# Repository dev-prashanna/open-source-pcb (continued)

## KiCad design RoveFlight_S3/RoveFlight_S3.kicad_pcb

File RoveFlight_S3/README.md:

# RoveFlight S3

**RF-S3-A0 — compact ESP32-S3 flight-controller engineering prototype for a 1S brushed quadcopter.**

Hardware layout release completed 2026-11-09: **ERC 0, DRC 0, unconnected items 0, schematic/PCB parity issues 0**, with all 15 independent connectivity checks passing. [Manufacturing package](fabrication/) and [validation evidence](docs/Manufacturing_Readiness.md) are included. Via-in-pad filling/capping and fabricator DFM are required; physical qualification remains open.

A real native KiCad design with ESP32-S3-WROOM-1-N8R2, four independent brushed-motor MOSFET stages, a hardware arming latch and watchdog, BMI270 SPI IMU, BMP390 SPI barometer, battery voltage/current monitoring, downward VL53L1X, IR receiver, USB-C and receiver/optical-flow/debug expansion.

Open **RoveFlight_S3.kicad_pro** in KiCad 10. The root schematic links the functional sheets. The PCB is 45 x 45 mm, six layers, nominal 1.0-mm thickness, two-sided assembly, with 25.5-mm-square M2 mounting and an antenna overhang. The assembled antenna extends 6.75 mm beyond the forward edge. No flight-ready, fabricated-board, RF, thermal or EMC qualification is claimed.

## Electrical limits

- Protected 1S LiPo, 3.1–4.2 V. No onboard charger or cell-protection IC.
- Brushed motors only. Proposed envelope: 1 A continuous per motor, 4 A aggregate, 2 A single-channel stall for at most 100 ms, subject to actual motor/propeller and thermal qualification.
- All external signals are 3.3 V. Receiver supply/interface compatibility must be checked; no 5-V UART tolerance or SBUS inverter is provided.
- Remove JP1 to disconnect motor enable physically. USB insertion clears the arming latch. Every detected fault requires a fresh arming command; see the exact reset caveat in the safety document.
- Local attitude stabilization, failsafes, calibration, PID, mixing, telemetry, configuration, OTA and logging require firmware. The supplied bring-up skeleton only holds motors disabled and blinks the status LED.

## Engineering documentation

- [Motor numbering, calculations and interlock](docs/Motors_and_Safety.md)
- [Battery and power architecture](docs/Power_Architecture.md)
- [GPIO allocation](docs/GPIO_Allocation.md)
- [Sensor orientation and mechanics](docs/Sensors_and_Mechanics.md)
- [Recommended firmware architecture](docs/Firmware_Architecture.md)
- [Bring-up and qualification procedure](docs/Bringup_and_Validation.md)
- [Manufacturing readiness](docs/Manufacturing_Readiness.md)

BOM.csv and BOM_Grouped.csv include part numbers and footprint assignments. GPIO_Allocation.csv, Connector_Pinouts.csv and Placement.csv provide machine-readable implementation references. Manufacturer sources are recorded in datasheets/sources.json. Manufacturer catalogue listing was checked for the N8R2 variant; no distributor stock reservation or guaranteed BOM availability is claimed.

The N8R2 variant provides 8-MB Quad SPI flash and 2-MB Quad PSRAM in an 18 x 25.5 x 3.1-mm module. N8 without PSRAM was considered but leaves less buffering for logs/telemetry; N8R8 adds memory and a different memory configuration without a need in this initial design. Neither is an automatic assembly substitution. The antenna carrier-board keepout follows the official module footprint and Espressif hardware guidelines; frame, battery and wiring clearance still need RF validation.

## Construction and verification

To check and export the current design without rebuilding its placement or routing, run `python scripts/release.py` in the configured Python environment. It gates manufacturing exports on ERC, DRC, parity and connectivity checks. Verify the resulting package from this directory with `sha256sum -c fabrication/SHA256SUMS`.

Scripts require KiCad 10 system Python bindings and requirements.txt. The project was initialized and the controller instantiated through the connected KiCad MCP server; native Python construction expands the complete hierarchical schematic and board using installed KiCad libraries and an explicit pin-to-net manifest. MCP/CLI ERC and DRC provide independent validation.

The construction sequence is build_design.py -> KiCad XML netlist export -> layout.py -> prepare_routing.py -> assisted Specctra routing -> import_routing.py -> any documented repairs -> silkscreen.py -> audit_design.py and final ERC/DRC/export. **build_design.py rebuilds the schematic; layout.py clears routing. Work on a copy when experimenting.** These are engineering construction scripts, not a flight-qualified unattended release pipeline.

Original project assets are licensed under CERN-OHL-P-2.0; see LICENSE. KiCad library-derived content retains its upstream licence and exception, recorded in libraries/README.md and libraries/KiCad-LICENSE.md.

[Bottom assembly preview](previews/PCB_bottom.png). Renders show assigned library models; missing connector/sensor models are represented by their board land patterns.

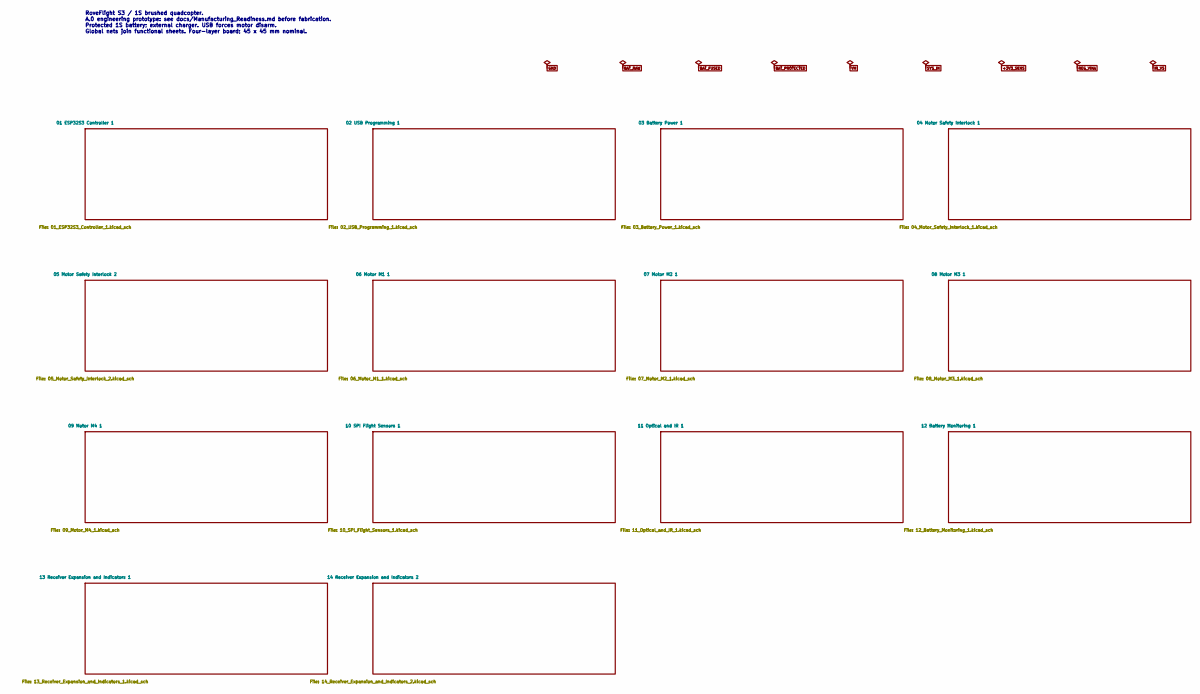
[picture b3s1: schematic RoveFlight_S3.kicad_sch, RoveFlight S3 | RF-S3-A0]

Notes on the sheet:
RoveFlight S3 / 1S brushed quadcopter. A.0 engineering prototype: see docs/Manufacturing_Readiness.md before fabrication. Protected 1S battery; external charger. USB forces motor disarm. Global nets join functional sheets. Four-layer board; 45 x 45 mm nominal.

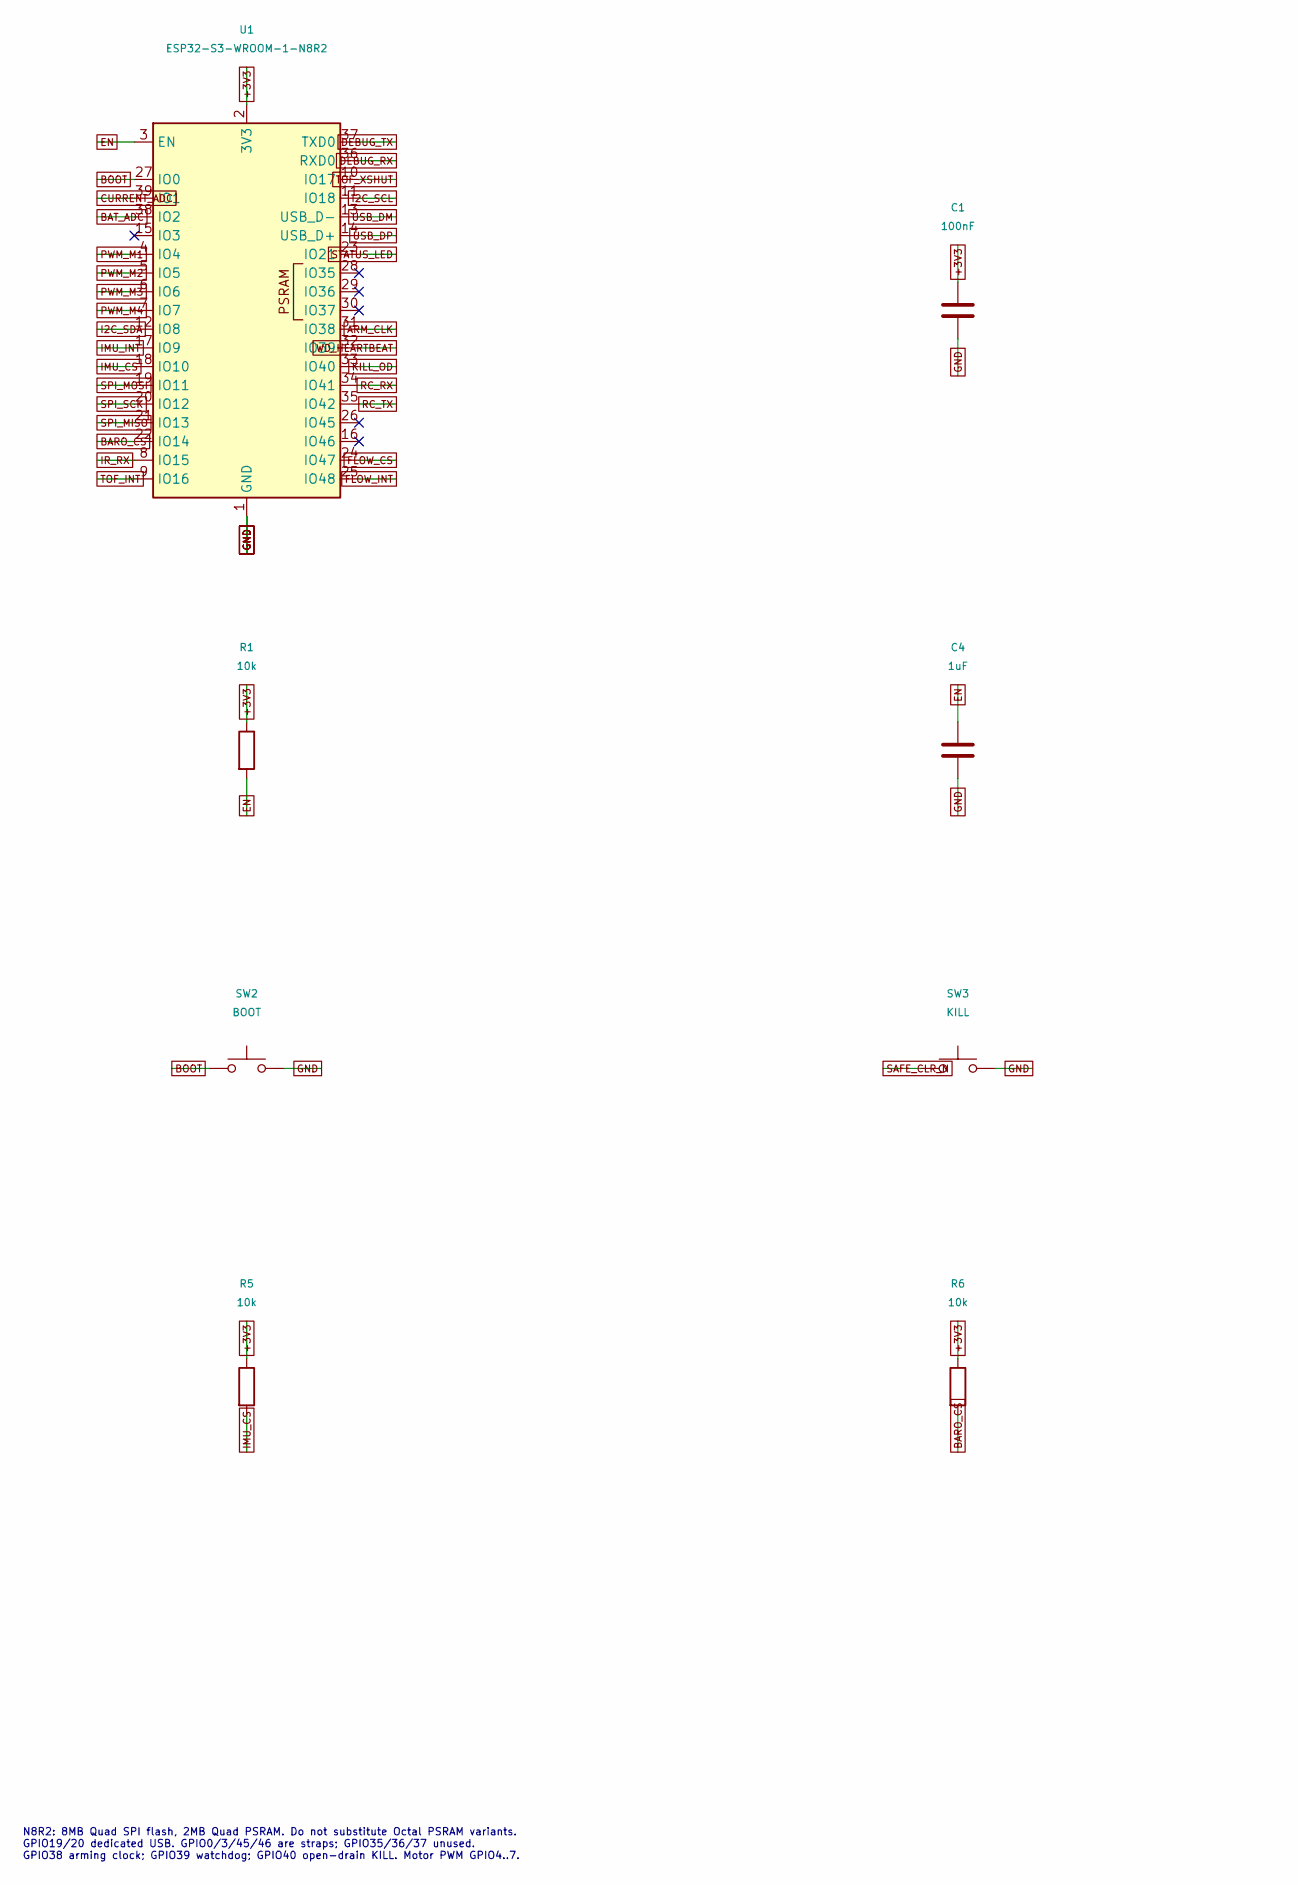
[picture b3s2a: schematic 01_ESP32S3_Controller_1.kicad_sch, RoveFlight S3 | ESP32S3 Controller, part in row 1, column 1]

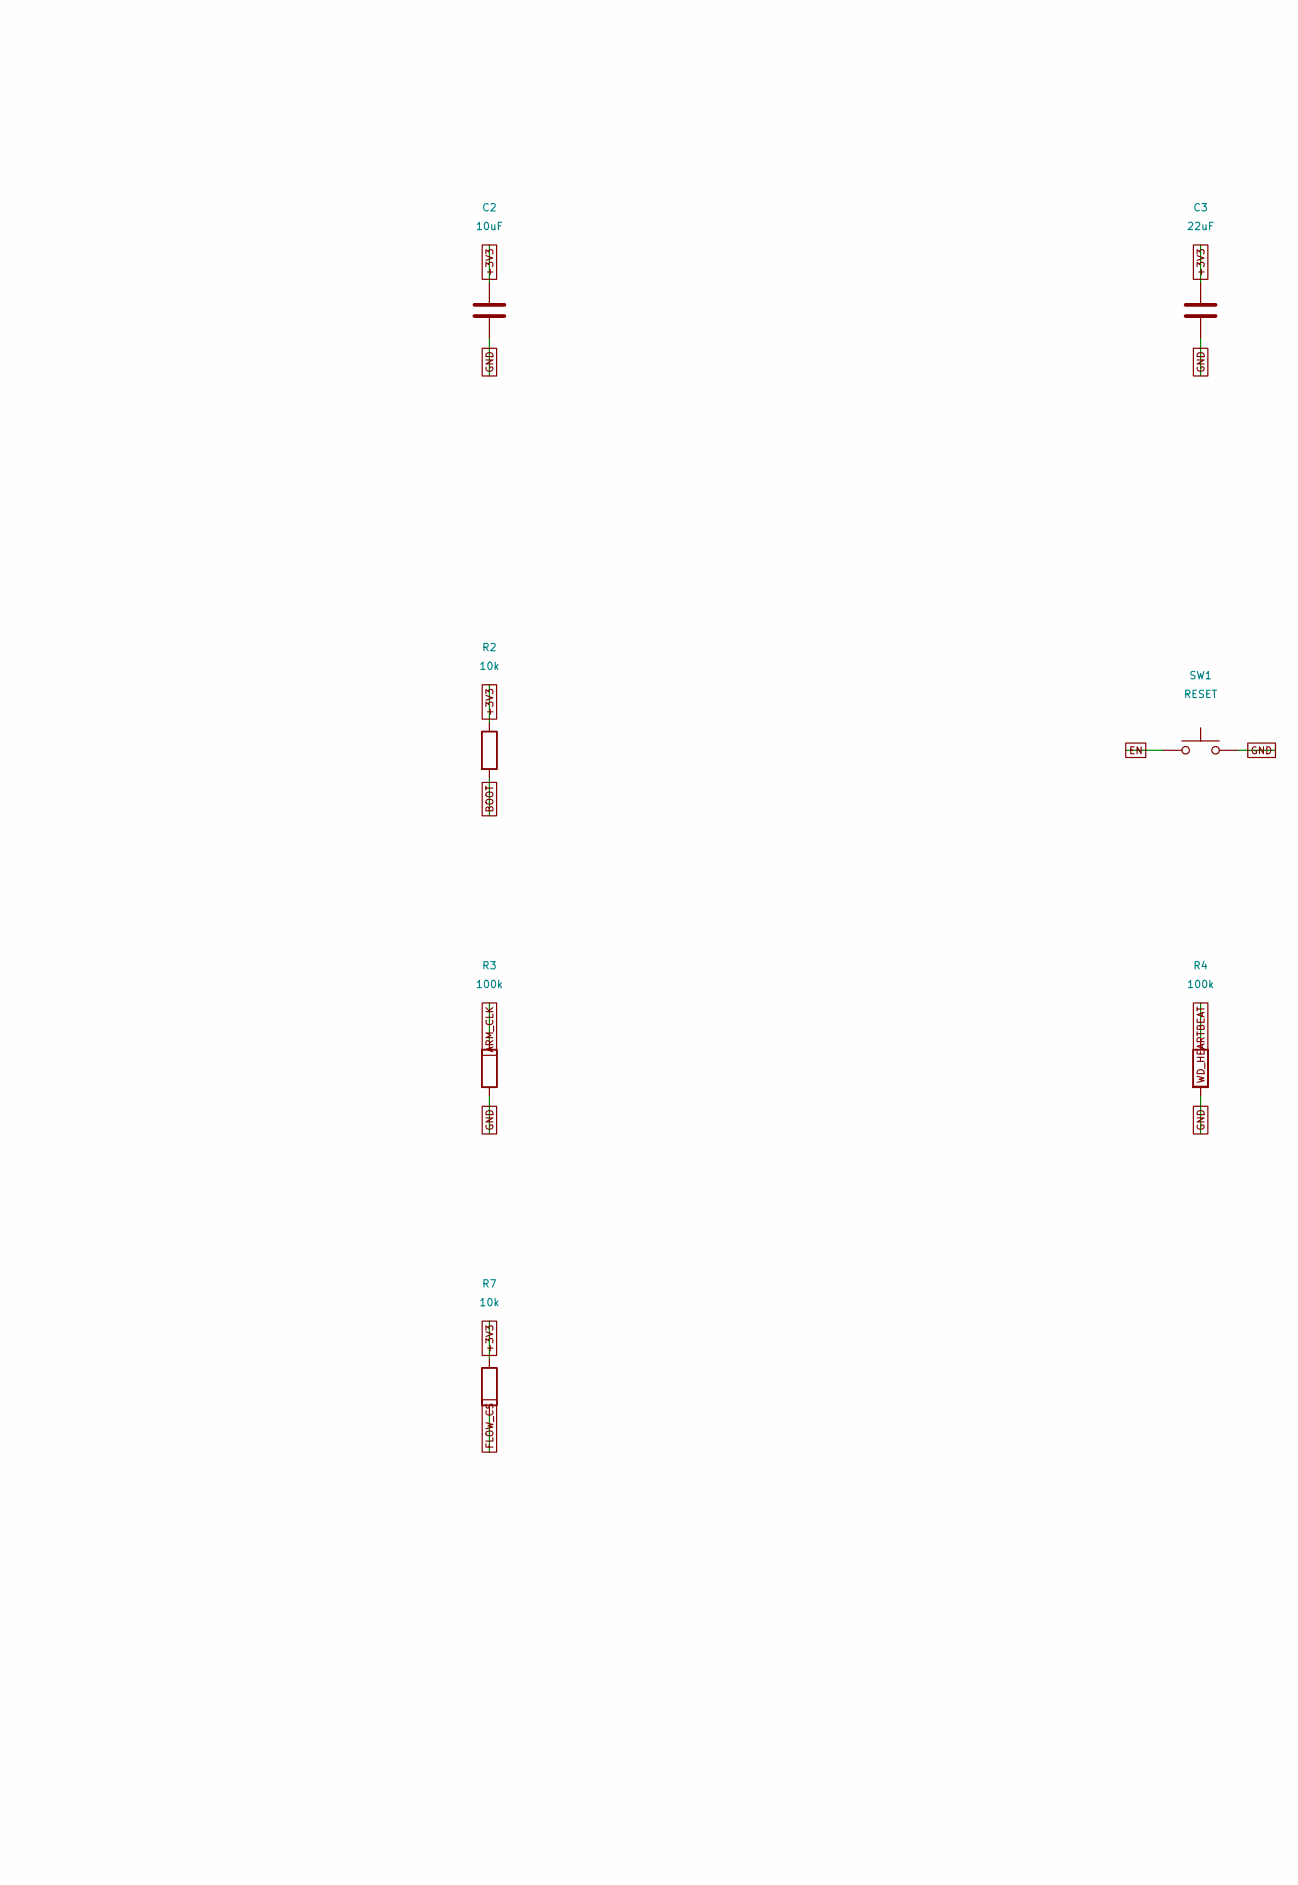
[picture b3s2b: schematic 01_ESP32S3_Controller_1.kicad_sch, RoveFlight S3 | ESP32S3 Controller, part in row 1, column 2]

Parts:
C1: 100nF; C_0402_1005Metric_RF_C1; MPN GRM155R71C104KA88D
C2: 10uF; C_0603_1608Metric; MPN GRM188R60J106ME47D
C3: 22uF; C_0805_2012Metric; MPN GRM21BR60J226ME39L
C4: 1uF; C_0402_1005Metric_RF_C4; MPN GRM155R61A105KE15D
R1: 10k; R_0402_1005Metric_RF_R1; MPN RC0402FR-071002L
R2: 10k; R_0402_1005Metric_RF_R2; MPN RC0402FR-071002L
R3: 100k; R_0402_1005Metric_RF_R3; MPN RC0402FR-071003L
R4: 100k; R_0402_1005Metric_RF_R4; MPN RC0402FR-071003L
R5: 10k; R_0402_1005Metric_RF_R5; MPN RC0402FR-071002L
R6: 10k; R_0402_1005Metric_RF_R6; MPN RC0402FR-071002L
R7: 10k; R_0402_1005Metric_RF_R7; MPN RC0402FR-071002L
SW1: RESET; SW_Push_1P1T-SH_NO_CK_KMR2xxG; MPN KMR221GLFS
SW2: BOOT; SW_Push_1P1T-SH_NO_CK_KMR2xxG; MPN KMR221GLFS
SW3: KILL; SW_Push_1P1T-SH_NO_CK_KMR2xxG; MPN KMR221GLFS
U1: ESP32-S3-WROOM-1-N8R2; ESP32-S3-WROOM-1_Overhang; MPN ESP32-S3-WROOM-1-N8R2

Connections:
+3V3: C1.1, C2.1, C3.1, R1.1, R2.1, R5.1, R6.1, R7.1, U1.2 (3V3); also elsewhere on the board
ARM_CLK: R3.1, U1.31 (IO38); also elsewhere on the board
BARO_CS: R6.2, U1.22 (IO14); also elsewhere on the board
BAT_ADC: U1.38 (IO2); also elsewhere on the board
BOOT: R2.2, SW2.1, U1.27 (IO0); also elsewhere on the board
CURRENT_ADC: U1.39 (IO1); also elsewhere on the board
DEBUG_RX: U1.36 (RXD0); also elsewhere on the board
DEBUG_TX: U1.37 (TXD0); also elsewhere on the board
EN: C4.1, R1.2, SW1.1, U1.3 (EN); also elsewhere on the board
FLOW_CS: R7.2, U1.24 (IO47); also elsewhere on the board
FLOW_INT: U1.25 (IO48); also elsewhere on the board
GND: C1.2, C2.2, C3.2, C4.2, R3.2, R4.2, SW1.2, SW2.2, SW3.2, U1.1 (GND), U1.40 (GND), U1.41 (GND); also elsewhere on the board
I2C_SCL: U1.11 (IO18); also elsewhere on the board
I2C_SDA: U1.12 (IO8); also elsewhere on the board
IMU_CS: R5.2, U1.18 (IO10); also elsewhere on the board
IMU_INT: U1.17 (IO9); also elsewhere on the board
IR_RX: U1.8 (IO15); also elsewhere on the board
KILL_OD: U1.33 (IO40); also elsewhere on the board
PWM_M1: U1.4 (IO4); also elsewhere on the board
PWM_M2: U1.5 (IO5); also elsewhere on the board
PWM_M3: U1.6 (IO6); also elsewhere on the board
PWM_M4: U1.7 (IO7); also elsewhere on the board
RC_RX: U1.34 (IO41); also elsewhere on the board
RC_TX: U1.35 (IO42); also elsewhere on the board
SAFE_CLR_N: SW3.1; also elsewhere on the board
SPI_MISO: U1.21 (IO13); also elsewhere on the board
SPI_MOSI: U1.19 (IO11); also elsewhere on the board
SPI_SCK: U1.20 (IO12); also elsewhere on the board
STATUS_LED: U1.23 (IO21); also elsewhere on the board
TOF_INT: U1.9 (IO16); also elsewhere on the board
TOF_XSHUT: U1.10 (IO17); also elsewhere on the board
USB_DM: U1.13 (USB_D-); also elsewhere on the board
USB_DP: U1.14 (USB_D+); also elsewhere on the board
WD_HEARTBEAT: R4.1, U1.32 (IO39); also elsewhere on the board

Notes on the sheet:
N8R2: 8MB Quad SPI flash, 2MB Quad PSRAM. Do not substitute Octal PSRAM variants. GPIO19/20 dedicated USB. GPIO0/3/45/46 are straps; GPIO35/36/37 unused. GPIO38 arming clock; GPIO39 watchdog; GPIO40 open-drain KILL. Motor PWM GPIO4..7.

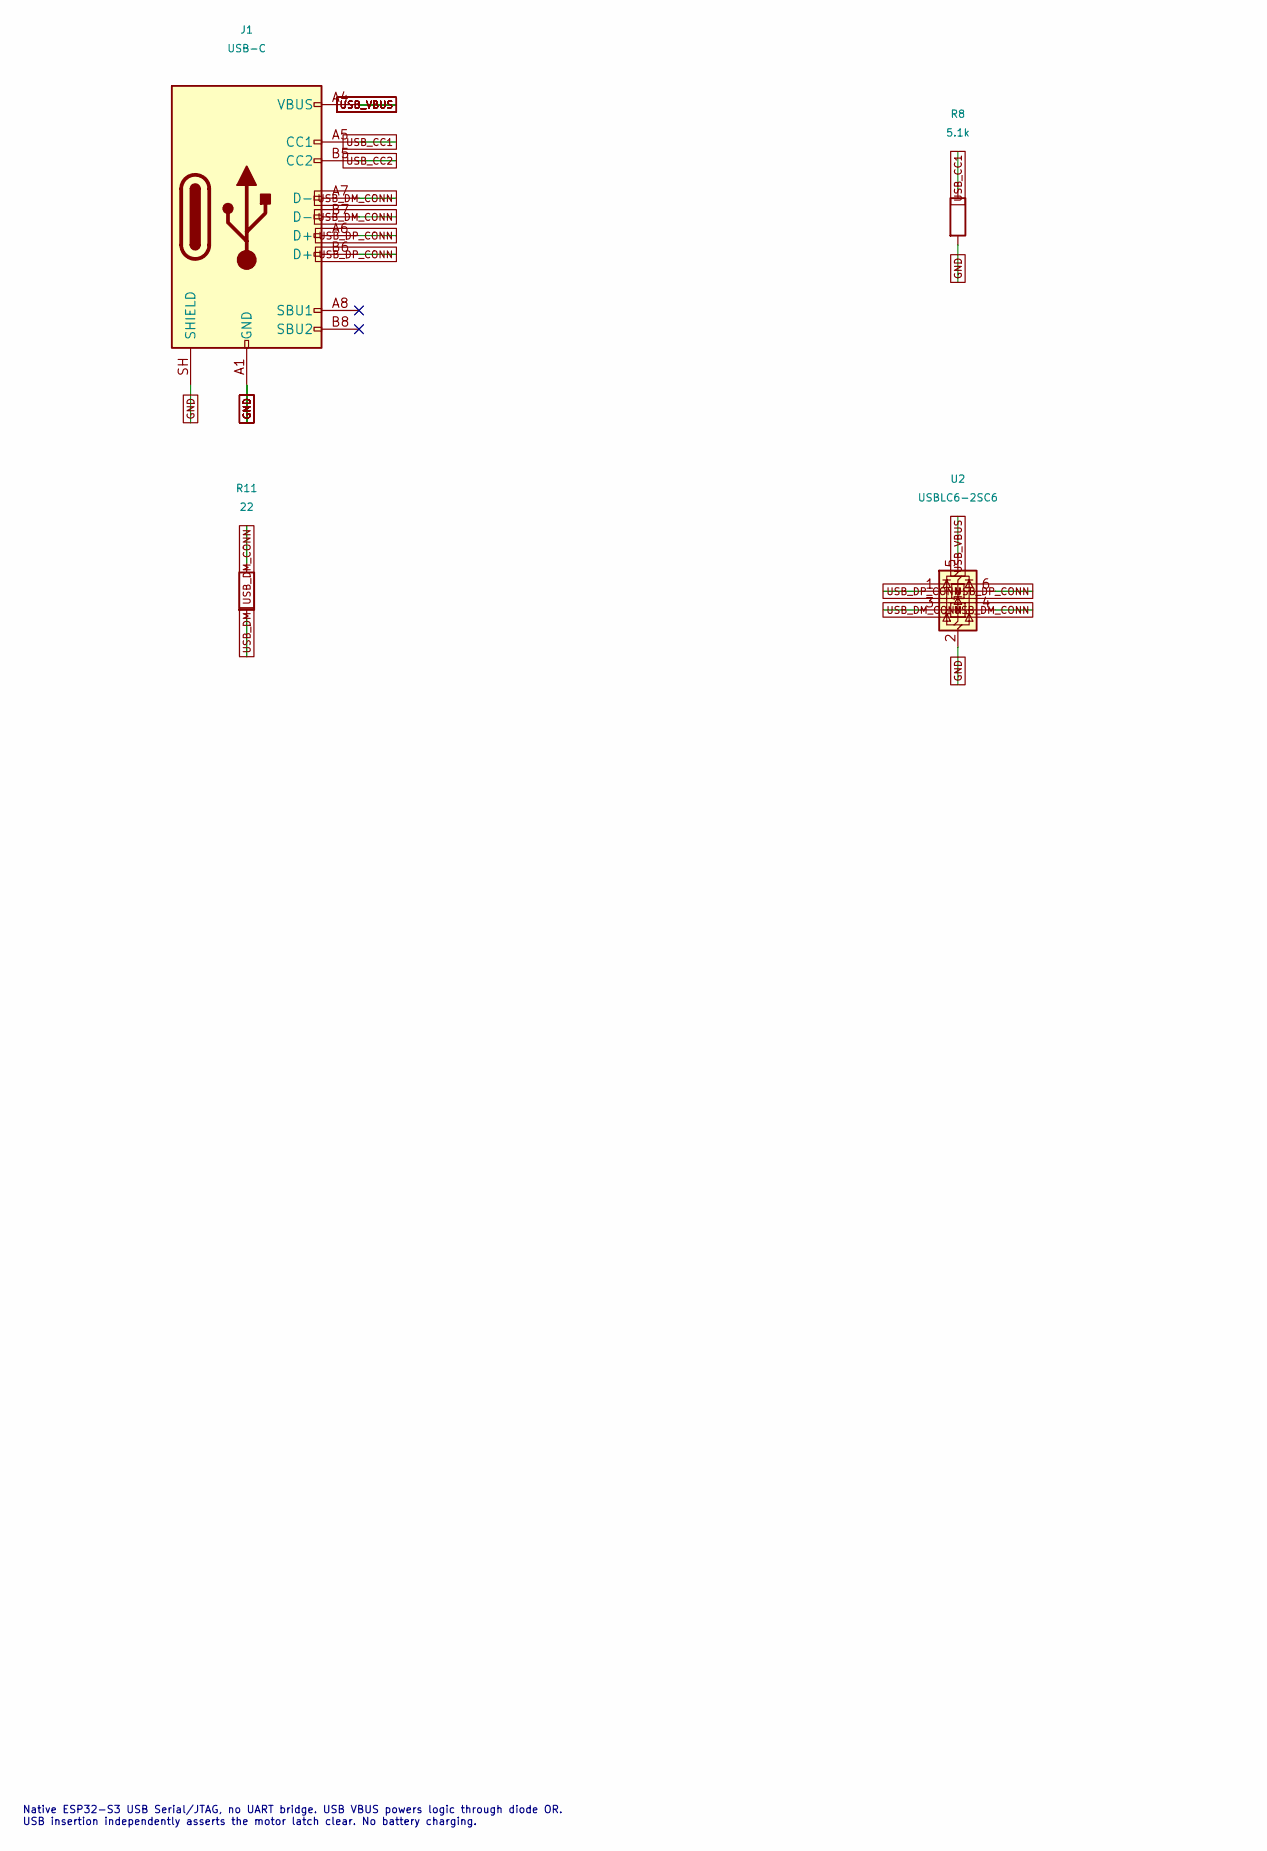
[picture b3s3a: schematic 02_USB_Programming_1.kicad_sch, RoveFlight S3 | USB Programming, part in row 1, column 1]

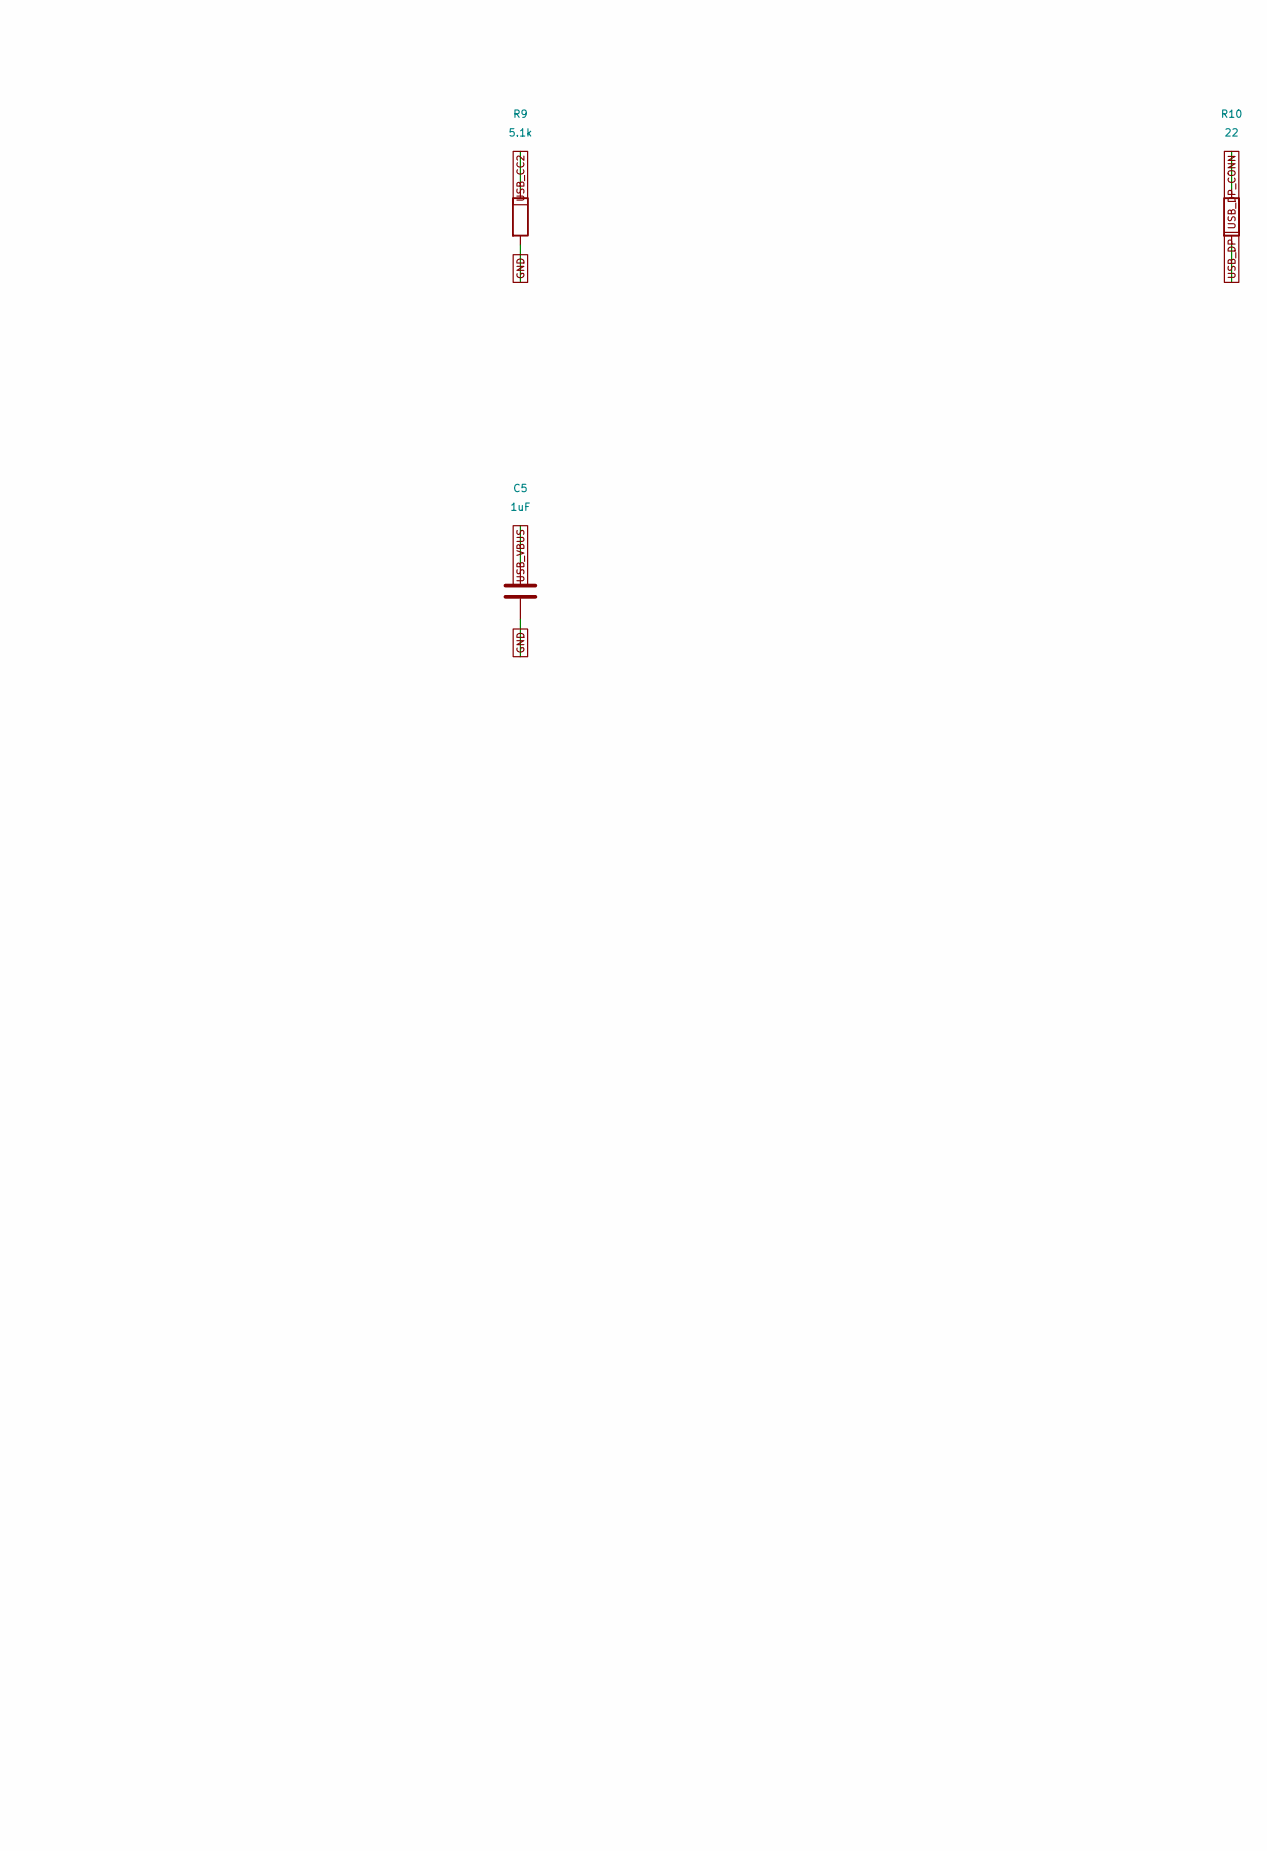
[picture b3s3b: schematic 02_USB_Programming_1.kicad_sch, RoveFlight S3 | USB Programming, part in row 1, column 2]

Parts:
C5: 1uF; C_0402_1005Metric_RF_C5; MPN GRM155R61A105KE15D
J1: USB-C; USB_C_Receptacle_HRO_TYPE-C-31-M-12; MPN TYPE-C-31-M-12
R8: 5.1k; R_0402_1005Metric_RF_R8; MPN RC0402FR-075101L
R9: 5.1k; R_0402_1005Metric_RF_R9; MPN RC0402FR-075101L
R10: 22; R_0402_1005Metric_RF_R10; MPN RC0402FR-0722R0L
R11: 22; R_0402_1005Metric_RF_R11; MPN RC0402FR-0722R0L
U2: USBLC6-2SC6; SOT-23-6; MPN USBLC6-2SC6

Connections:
GND: C5.2, J1.A1 (GND), J1.A12 (GND), J1.B1 (GND), J1.B12 (GND), J1.SH (SHIELD), R8.2, R9.2, U2.2 (GND); also elsewhere on the board
USB_CC1: J1.A5 (CC1), R8.1
USB_CC2: J1.B5 (CC2), R9.1
USB_DM: R11.2; also elsewhere on the board
USB_DM_CONN: J1.A7 (D-), J1.B7 (D-), R11.1, U2.3 (I/O2), U2.4 (I/O2)
USB_DP: R10.2; also elsewhere on the board
USB_DP_CONN: J1.A6 (D+), J1.B6 (D+), R10.1, U2.1 (I/O1), U2.6 (I/O1)
USB_VBUS: C5.1, J1.A4 (VBUS), J1.A9 (VBUS), J1.B4 (VBUS), J1.B9 (VBUS), U2.5 (VBUS); also elsewhere on the board

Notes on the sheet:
Native ESP32-S3 USB Serial/JTAG, no UART bridge. USB VBUS powers logic through diode OR. USB insertion independently asserts the motor latch clear. No battery charging.

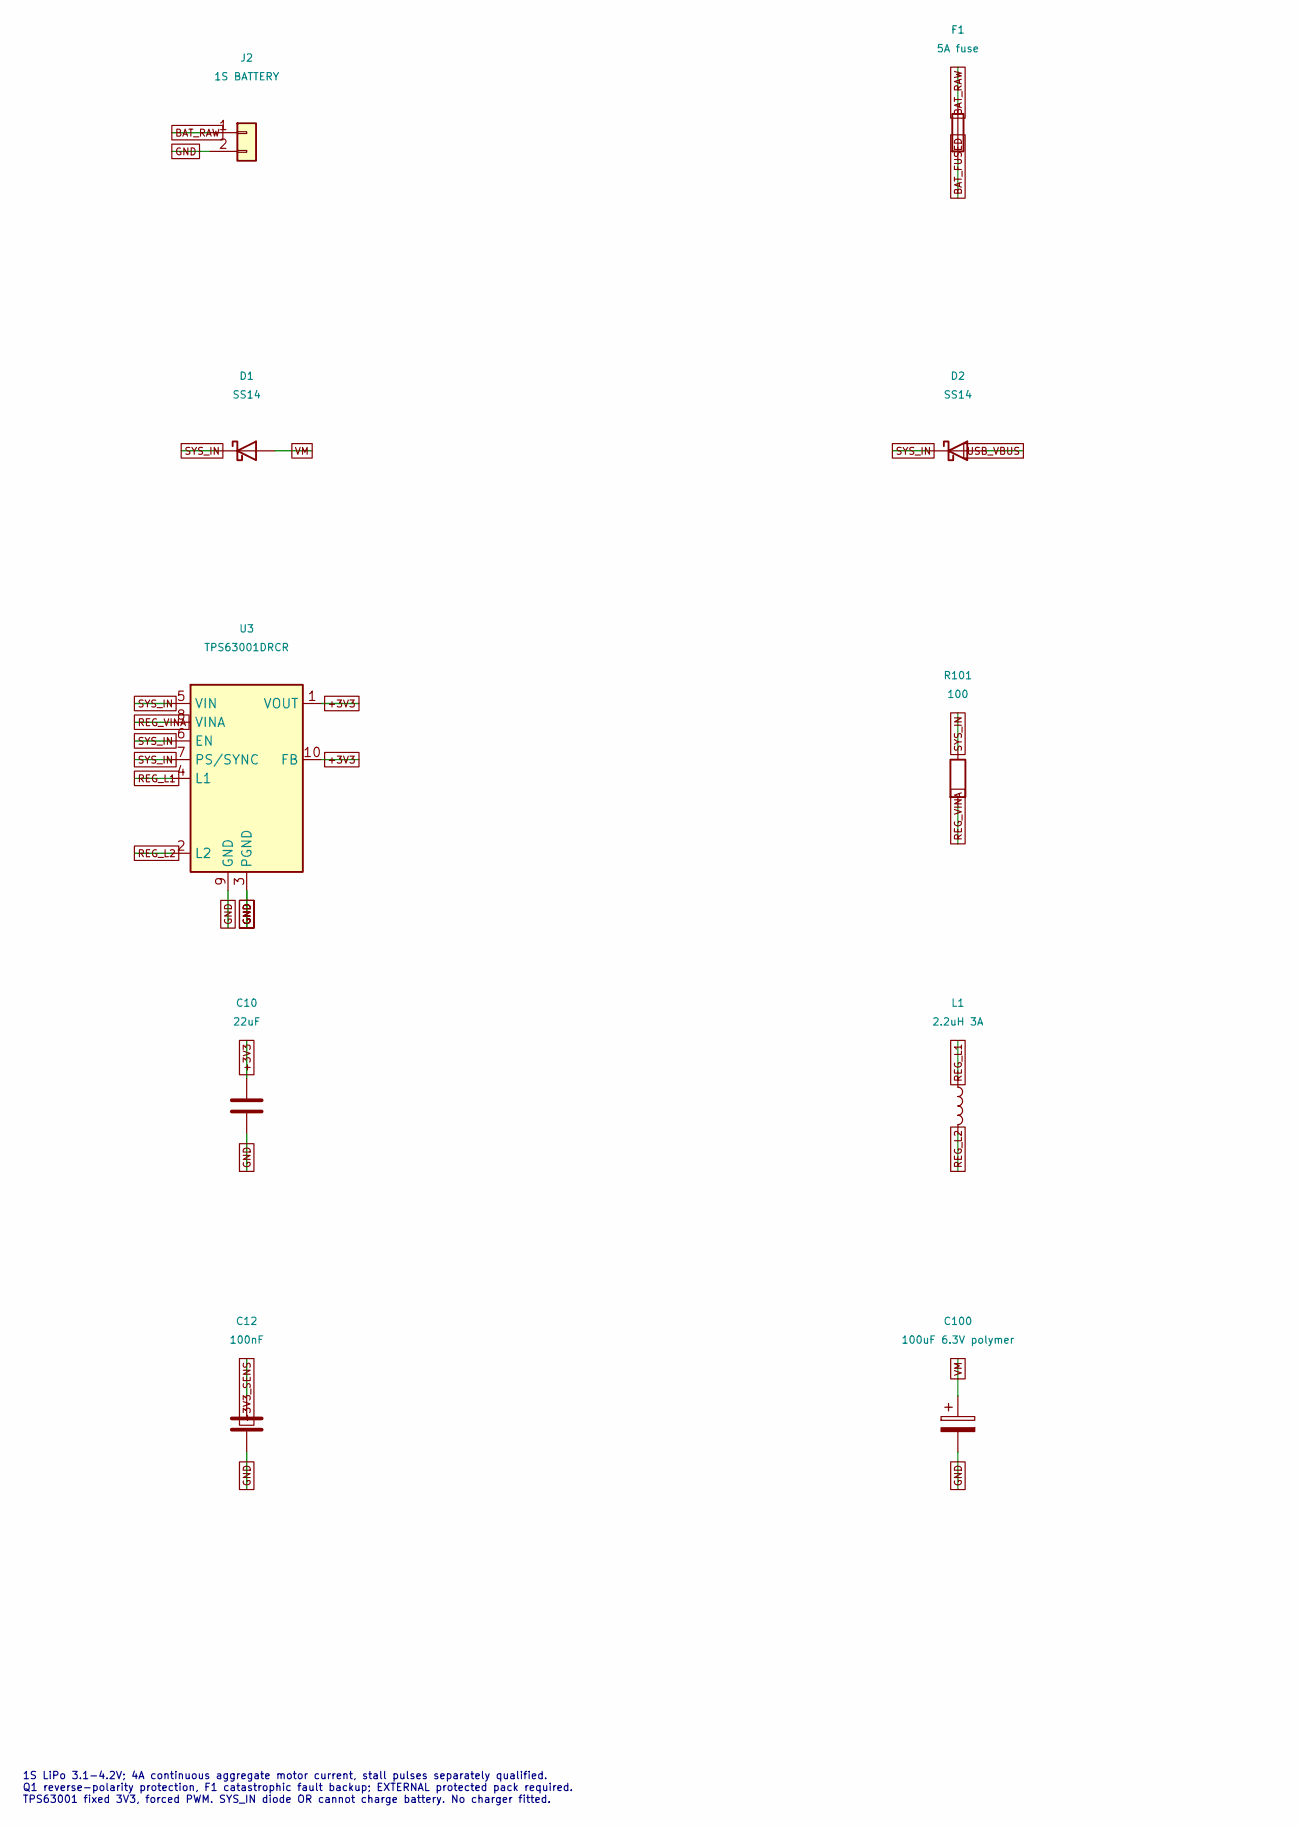
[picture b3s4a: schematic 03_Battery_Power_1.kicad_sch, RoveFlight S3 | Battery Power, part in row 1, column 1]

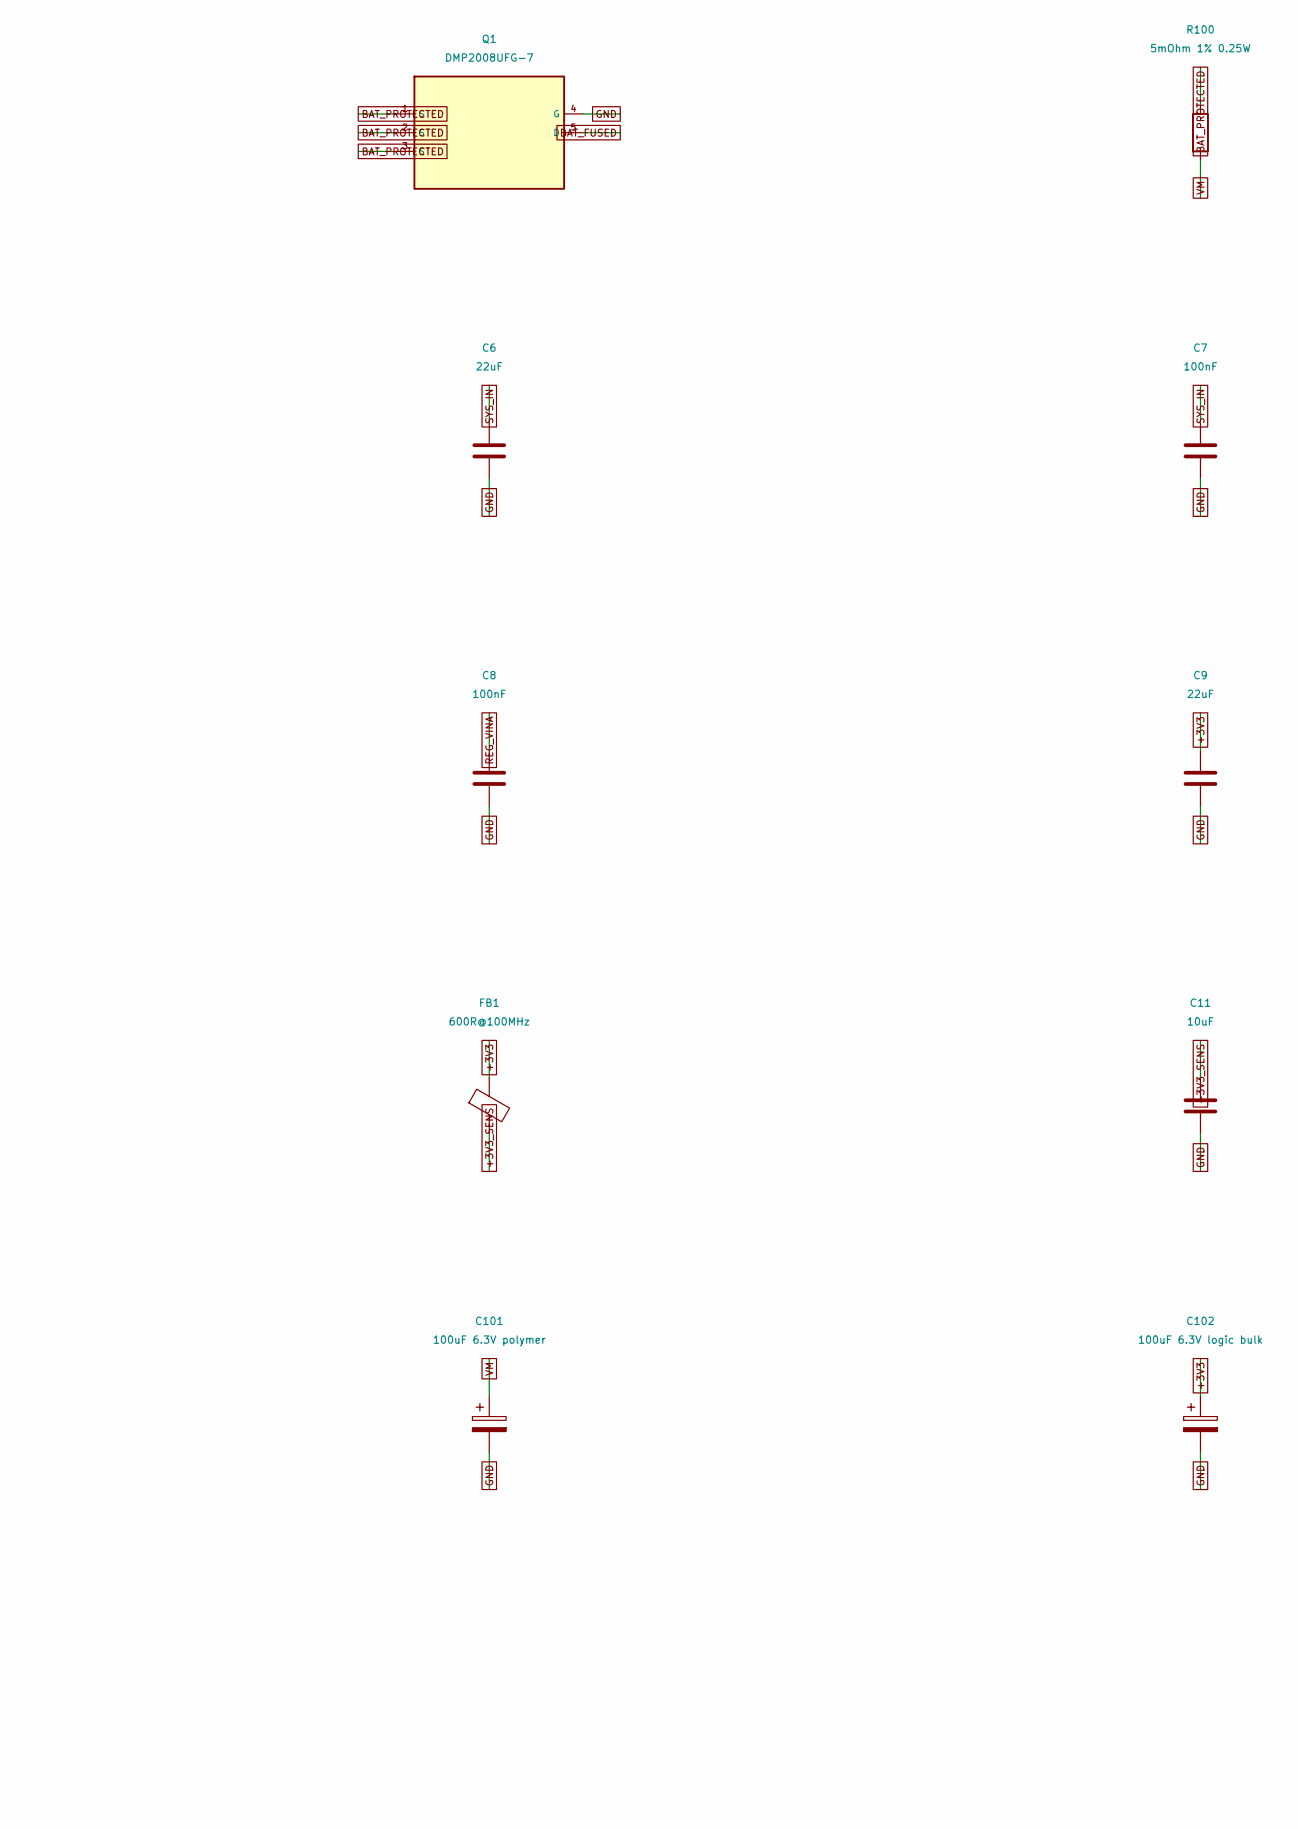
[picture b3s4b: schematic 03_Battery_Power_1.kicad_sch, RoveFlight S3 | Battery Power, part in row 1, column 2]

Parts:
C6, C9, C10: 22uF; C_0805_2012Metric; MPN GRM21BR60J226ME39L
C7: 100nF; C_0402_1005Metric_RF_C7; MPN GRM155R71C104KA88D
C8: 100nF; C_0402_1005Metric_RF_C8; MPN GRM155R71C104KA88D
C11: 10uF; C_0603_1608Metric; MPN GRM188R60J106ME47D
C12: 100nF; C_0402_1005Metric_RF_C12; MPN GRM155R71C104KA88D
C100, C101: 100uF 6.3V polymer; CP_EIA-3528-21_Kemet-B; MPN T520B107M006ATE070
C102: 100uF 6.3V logic bulk; CP_EIA-3528-21_Kemet-B; MPN T520B107M006ATE070
D1, D2: SS14; D_SMA; MPN SS14-13-F
F1: 5A fuse; Fuse_1206_3216Metric; MPN 0467005.NR
FB1: 600R@100MHz; L_0603_1608Metric; MPN BLM18AG601SN1D
J2: 1S BATTERY; BatteryPads; MPN PCB_SOLDER_PADS_20AWG
L1: 2.2uH 3A; L_Vishay_IFSC-1515AH_4x4x1.8mm; MPN IFSC1515AHER2R2M01
Q1: DMP2008UFG-7; Diodes_PowerDI3333-8; MPN DMP2008UFG-7
R100: 5mOhm 1% 0.25W; R_1206_3216Metric; MPN WSL1206R0050FEA
R101: 100; R_0402_1005Metric_RF_R101; MPN RC0402FR-071000L
U3: TPS63001DRCR; Texas_DRC0010J_ThermalVias_RF_U3; MPN TPS63001DRCR

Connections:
+3V3: C9.1, C10.1, C102.1, FB1.1, U3.1 (VOUT), U3.10 (FB); also elsewhere on the board
+3V3_SENS: C11.1, C12.1, FB1.2; also elsewhere on the board
BAT_FUSED: F1.2, Q1.5 (D)
BAT_PROTECTED: Q1.1 (S), Q1.2 (S), Q1.3 (S), R100.1; also elsewhere on the board
BAT_RAW: F1.1, J2.1
GND: C6.2, C7.2, C8.2, C9.2, C10.2, C11.2, C12.2, C100.2, C101.2, C102.2, J2.2, Q1.4 (G), U3.3 (PGND), U3.9 (GND), U3.11 (PGND); also elsewhere on the board
REG_L1: L1.1, U3.4 (L1)
REG_L2: L1.2, U3.2 (L2)
REG_VINA: C8.1, R101.2, U3.8 (VINA)
SYS_IN: C6.1, C7.1, D1.1 (K), D2.1 (K), R101.1, U3.5 (VIN), U3.6 (EN), U3.7 (PS/SYNC)
USB_VBUS: D2.2 (A); also elsewhere on the board
VM: C100.1, C101.1, D1.2 (A), R100.2; also elsewhere on the board

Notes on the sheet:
1S LiPo 3.1-4.2V; 4A continuous aggregate motor current, stall pulses separately qualified. Q1 reverse-polarity protection, F1 catastrophic fault backup; EXTERNAL protected pack required. TPS63001 fixed 3V3, forced PWM. SYS_IN diode OR cannot charge battery. No charger fitted.

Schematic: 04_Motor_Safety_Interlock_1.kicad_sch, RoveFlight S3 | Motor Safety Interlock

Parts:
C103: 100nF; C_0402_1005Metric_RF_C103; MPN GRM155R71C104KA88D
C104: 1nF; C_0402_1005Metric_RF_C104; MPN GRM1555C1H102JA01D
C105: 100nF; C_0402_1005Metric_RF_C105; MPN GRM155R71C104KA88D
C106: 10nF; C_0402_1005Metric_RF_C106; MPN GRM155R71H103KA88D
C107: 10nF; C_0402_1005Metric_RF_C107; MPN GRM155R71H103KA88D
C108: 100nF; C_0402_1005Metric_RF_C108; MPN GRM155R71C104KA88D
C109: 100nF; C_0402_1005Metric_RF_C109; MPN GRM155R71C104KA88D
JP1: REMOVE TO DISARM; PinHeader_1x02_P1.27mm_Vertical; MPN 20021111-00002T4LF
Q2: 2N7002; SOT-23; MPN 2N7002
R102: 665k; R_0402_1005Metric_RF_R102; MPN RC0402FR-076653L
R103: 100k; R_0402_1005Metric_RF_R103; MPN RC0402FR-071003L
R104: 10k; R_0402_1005Metric_RF_R104; MPN RC0402FR-071002L
R105: 1k; R_0402_1005Metric_RF_R105; MPN RC0402FR-071001L
R106: 100k; R_0402_1005Metric_RF_R106; MPN RC0402FR-071003L
R107: 1M; R_0402_1005Metric_RF_R107; MPN RC0402FR-071004L
R108: 10k; R_0402_1005Metric_RF_R108; MPN RC0402FR-071002L
U4: TPS3431SDRBR; Texas_DRB0008A; MPN TPS3431SDRBR
U5: TPS3808G01DBVR; SOT-23-6; MPN TPS3808G01DBVR
U6: SN74LVC1G74DCUR; VSSOP-8_2.3x2mm_P0.5mm; MPN SN74LVC1G74DCUR

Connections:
+3V3: C103.1, C105.1, C108.1, C109.1, R104.1, R108.1, U4.1 (VDD), U4.3 (EN), U4.5 (SET1), U5.6 (VDD), U6.2 (D), U6.7 (PRE_N), U6.8 (VCC); also elsewhere on the board
ARMED: U6.5 (Q); also elsewhere on the board
ARMED_N: JP1.1, U6.3 (Q_N)
ARM_CLK: U6.1 (CLK); also elsewhere on the board
EN: U5.3 (~MR); also elsewhere on the board
GND: C103.2, C104.2, C105.2, C106.2, C107.2, C108.2, C109.2, Q2.2 (S), R103.2, R107.2, U4.4 (GND), U4.9 (EP), U5.2 (GND), U6.4 (GND); also elsewhere on the board
KILL_OD: R105.1; also elsewhere on the board
MOTOR_OE_N: JP1.2, R108.2; also elsewhere on the board
SAFE_CLR_N: Q2.3 (D), R104.2, R105.2, U4.7 (WDO_N), U5.1 (~RESET), U6.6 (CLR_N); also elsewhere on the board
USB_KILL_GATE: Q2.1 (G), R106.2, R107.1
USB_VBUS: R106.1; also elsewhere on the board
UV_DELAY: C106.1, U5.4 (CT)
UV_SENSE: C107.1, R102.2, R103.1, U5.5 (SENSE)
VM: R102.1; also elsewhere on the board
WD_HEARTBEAT: U4.6 (WDI); also elsewhere on the board
WD_TIMING: C104.1, U4.2 (CWD)

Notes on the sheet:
SAFE_CLR_N is wired-OR: watchdog, VM undervoltage, USB, KILL button, firmware OD. Async clear latches disarmed. A NEW rising ARM_CLK is required after every fault. JP1 physically disconnects enable. PWM gates high impedance when disarmed, with 10k gate pulldowns. Watchdog 1nF: 132.4ms nominal, fall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

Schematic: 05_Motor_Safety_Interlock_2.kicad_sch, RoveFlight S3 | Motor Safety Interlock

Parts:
U7: SN74LVC125APWR; TSSOP-14_4.4x5mm_P0.65mm; MPN SN74LVC125APWR

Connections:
+3V3: U7.14 (VCC); also elsewhere on the board
BUF_M1: U7.3; also elsewhere on the board
BUF_M2: U7.6; also elsewhere on the board
BUF_M3: U7.8; also elsewhere on the board
BUF_M4: U7.11; also elsewhere on the board
GND: U7.7 (GND); also elsewhere on the board
MOTOR_OE_N: U7.1, U7.4, U7.10, U7.13; also elsewhere on the board
PWM_M1: U7.2; also elsewhere on the board
PWM_M2: U7.5; also elsewhere on the board
PWM_M3: U7.9; also elsewhere on the board
PWM_M4: U7.12; also elsewhere on the board

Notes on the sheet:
SAFE_CLR_N is wired-OR: watchdog, VM undervoltage, USB, KILL button, firmware OD. Async clear latches disarmed. A NEW rising ARM_CLK is required after every fault. JP1 physically disconnects enable. PWM gates high impedance when disarmed, with 10k gate pulldowns. Watchdog 1nF: 132.4ms nominal, fall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
